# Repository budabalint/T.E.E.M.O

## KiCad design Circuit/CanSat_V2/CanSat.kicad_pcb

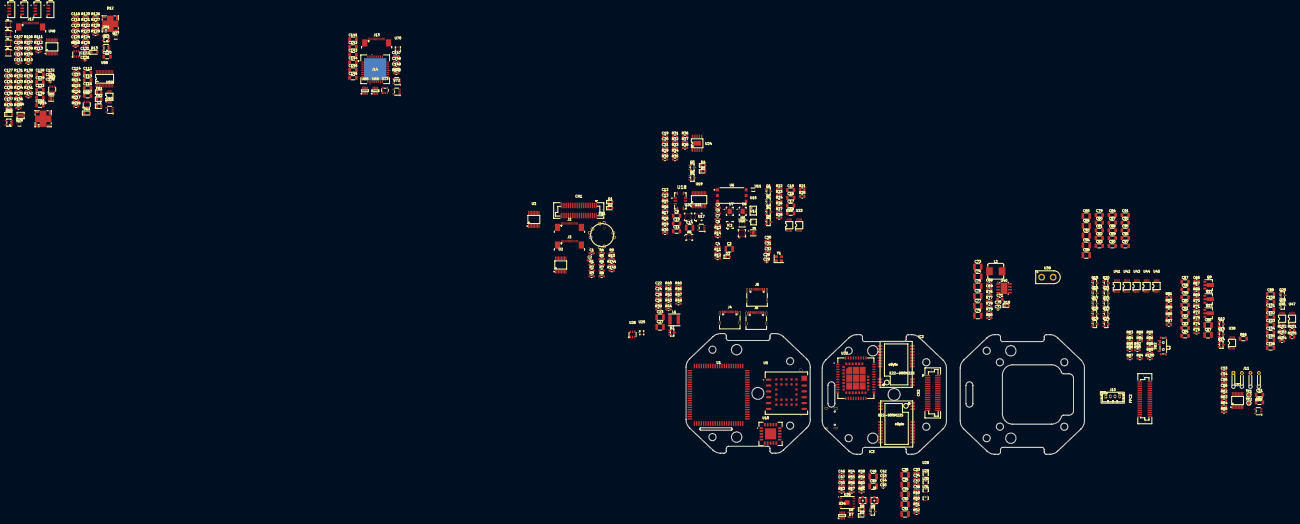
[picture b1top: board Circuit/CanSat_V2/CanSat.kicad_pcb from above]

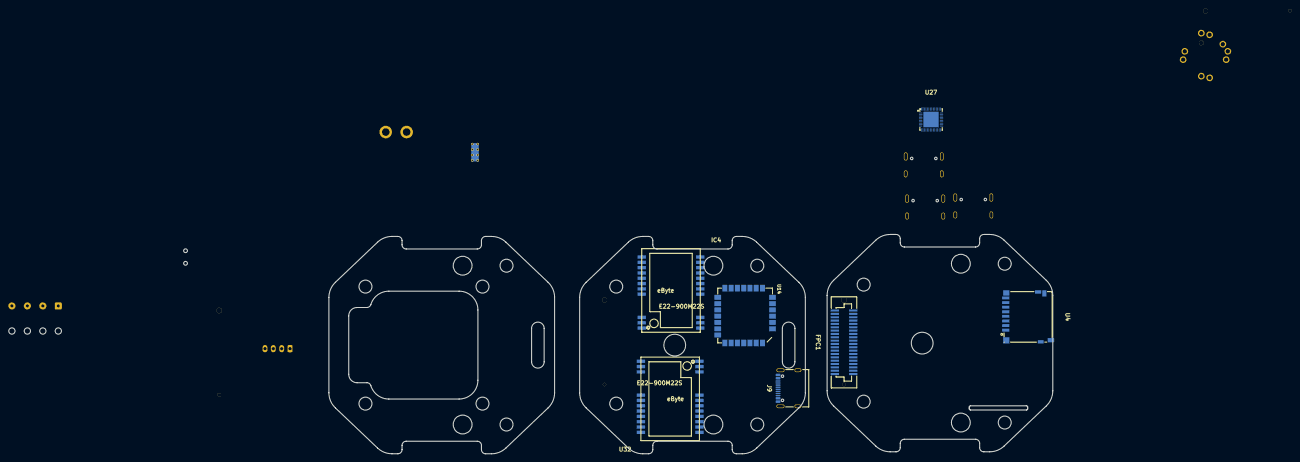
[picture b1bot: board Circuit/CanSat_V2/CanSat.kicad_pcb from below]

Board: 4 copper layers, 442 parts (7 on the bottom side), 345 nets, no tracks yet.

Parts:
C1, C2, C4, C5, C6, C7, C8, C12, C13, C19, C20, C21, C22, C24, C25, C26, C30, C31, C32, C33, C34, C37, C38, C46, C47, C50, C53, C54, C55, C56, C65, C68, C107, C108, C109, C110, C111, C114, C115, C118, C119, C123, C124, C125, C127, C130, C131, C135, C136, C137, C147, C148, C149: 100nF; C_0603_1608Metric_Pad1.08x0.95mm_HandSolder
C3, C14, C23, C27, C35, C36, C39, C40, C41, C48, C49, C66, C67, C73, C74, C75, C76, C77, C78, C85, C86, C93, C94, C98: 22uF; C_1210_3225Metric
C9, C10, C11, C15, C16, C17, C18, C51, C52, C57, C58, C59, C60, C61, C62, C63, C64, C79, C80, C81, C82, C83, C84, C87, C88, C89, C90, C91, C92, C95, C96, C97, C99, C100, C101, C102, C103, C104, C105, C106, C112, C113, C116, C117, C120, C128, C129, C133, C139, C140, C141, C142, C143, C144, C145, C146: 4.7uF; C_1206_3216Metric
C28, C29: 22pF; C_0402_1005Metric_Pad0.74x0.62mm_HandSolder
C42, C43, C44, C45: -; C_0402_1005Metric_Pad0.74x0.62mm_HandSolder
C69: 10nF; C_0603_1608Metric_Pad1.08x0.95mm_HandSolder
C70, C72: 68pF; C_0402_1005Metric_Pad0.74x0.62mm_HandSolder
C71: 1.2nF; C_0805_2012Metric_Pad1.18x1.45mm_HandSolder
C121: 10pF; C_0402_1005Metric_Pad0.74x0.62mm_HandSolder
C122: 47pF; C_0402_1005Metric_Pad0.74x0.62mm_HandSolder
C126, C138: 1nF; C_0402_1005Metric_Pad0.74x0.62mm_HandSolder
C132: 1pF; C_0402_1005Metric_Pad0.74x0.62mm_HandSolder
C134: 15pF; C_0402_1005Metric_Pad0.74x0.62mm_HandSolder
CN1, CN2: 61082-041402LF; CONN-SMD_61082-041402LF
D1, D2, D3, D4, D5, D8, D9, D10: LED; LED_0603_1608Metric_Pad1.05x0.95mm_HandSolder
D6, D7: ESD5311X-2/TR; D_0402_1005Metric_Pad0.77x0.64mm_HandSolder
D11: BAT54J; D_SOD-323_HandSoldering
D12, D14: SiPM; OPTO-SMD_4P-MICROFC-60035-SMT-TR
D13, D15: TECH PUBLIC BAS70WS; D_SOD-323_HandSoldering
FB1, FB2: FerriteBead_Small; D_0805_2012Metric
FPC1, FPC2: 61083-044402LF; FPC-SMD_40P-P0.80_61083-044402LF
IC1: ZMOD4510AI1V
IC2, IC3, IC4: E22-xxxM22S; E22-400M22S
J2, J3, J12, J13: Conn_01x15_Pin; TE_1-1734839-5_1x15-1MP_P0.5mm_Horizontal
J4, J5, J6, J9: USB_C; USB_C_Receptacle_Palconn_UTC16-G
J7, J8: U-Fl-IPEX; IPEX-SMD_4P-L2.6-W2.6-LS3.1
J10: VTX PWR; JST_PH_B4B-PH-K_1x04_P2.00mm_Vertical
J11: GLM-670; SolderWire-0.127sqmm_1x04_P3.7mm_D0.48mm_OD1mm_Relief
J14: FLIR_Lepton_Molex_1050281001; flir_CONN_1050282031_MOL
L1: SMNR4030-1R8MT; L_Taiyo-Yuden_NR-50xx
L2: FXL0630-3R3-M; L_Bourns_SRP7028A_7.3x6.6mm
L3: 47uh; D_0805_2012Metric
MT1: ICM-42670-P; XDCR_ICM-42670-P
Q1, Q3, Q15, Q16, Q19, Q20, Q23, Q25: AO3401A; SOT-23
Q2, Q4, Q5, Q6, Q7, Q8, Q10, Q17, Q18, Q21, Q22, Q24, Q26: BC817; SOT-23
Q9, Q11, Q12: WD070PG; SOT-89-3
Q13, Q14: AO3400A; SOT-23
Q27, Q28: XNRUSEMI XR2SK3019; SOT-523
R1, R121, R125, R129, R142: 33Ω; R_0603_1608Metric_Pad0.98x0.95mm_HandSolder
R2, R3, R4, R5: 2.2kΩ; R_0603_1608Metric_Pad0.98x0.95mm_HandSolder
R6, R10, R12: 220Ω; R_0603_1608Metric_Pad0.98x0.95mm_HandSolder
R7, R8, R9, R18, R19, R20, R22, R26, R29, R41, R55, R59, R67, R83, R84, R91, R92, R98, R102, R143, R144, R145: 47kΩ; R_0603_1608Metric_Pad0.98x0.95mm_HandSolder
R11, R24, R28, R34, R35, R36, R37, R46, R47, R48, R70, R71, R72, R87, R88, R95, R96, R100, R104, R122, R134: 10kΩ; R_0603_1608Metric_Pad0.98x0.95mm_HandSolder
R13: 18kΩ; R_0603_1608Metric_Pad0.98x0.95mm_HandSolder
R14, R38, R43, R128, R138, R139, R141: 100kΩ; R_0603_1608Metric_Pad0.98x0.95mm_HandSolder
R15: 20Ω; R_0603_1608Metric_Pad0.98x0.95mm_HandSolder
R16: 12.4Ω; R_0603_1608Metric_Pad0.98x0.95mm_HandSolder
R17: 42.2Ω; R_0603_1608Metric_Pad0.98x0.95mm_HandSolder
R21, R25, R81, R82, R89, R90, R97, R101, R105: shunt; R_0805_2012Metric
R23, R27, R58, R68, R69, R85, R86, R93, R94, R99, R103, R106, R107, R108, R109, R110, R111, R112, R113, R124: 4.7kΩ; R_0603_1608Metric_Pad0.98x0.95mm_HandSolder
R30, R31, R40, R42, R60, R61: 5.1kΩ; R_0603_1608Metric_Pad0.98x0.95mm_HandSolder
R32, R33, R56, R57, R62, R63, R64, R65, R73, R119, R123, R126, R127, R130, R136: 1kΩ; R_0603_1608Metric_Pad0.98x0.95mm_HandSolder
R39: 910kΩ; R_0603_1608Metric_Pad0.98x0.95mm_HandSolder
R44: 510kΩ; R_0603_1608Metric_Pad0.98x0.95mm_HandSolder
R45: 160kΩ; R_0603_1608Metric_Pad0.98x0.95mm_HandSolder
R49, R50, R51, R52, R80, R133: 100Ω; R_0603_1608Metric_Pad0.98x0.95mm_HandSolder
R53, R54: 0Ω; R_0603_1608Metric_Pad0.98x0.95mm_HandSolder
R66: shunt; R_1206_3216Metric
R74, R75: 200kΩ; R_0603_1608Metric_Pad0.98x0.95mm_HandSolder
R76: 10Ω; R_0603_1608Metric_Pad0.98x0.95mm_HandSolder
R77: 12kΩ; R_0603_1608Metric_Pad0.98x0.95mm_HandSolder
R78: 105kΩ; R_0603_1608Metric_Pad0.98x0.95mm_HandSolder
R79: 33kΩ; R_0603_1608Metric_Pad0.98x0.95mm_HandSolder
R114: 68kΩ; R_0603_1608Metric_Pad0.98x0.95mm_HandSolder
R115: 154kΩ; R_0603_1608Metric_Pad0.98x0.95mm_HandSolder
R116: 6,65kΩ; R_0603_1608Metric_Pad0.98x0.95mm_HandSolder
R117: 470kΩ; R_0603_1608Metric_Pad0.98x0.95mm_HandSolder
R118: 39kΩ; R_0603_1608Metric_Pad0.98x0.95mm_HandSolder
R120, R131: 470Ω; R_0603_1608Metric_Pad0.98x0.95mm_HandSolder
R132: 50Ω; R_0603_1608Metric_Pad0.98x0.95mm_HandSolder
R135: 680Ω; R_0603_1608Metric_Pad0.98x0.95mm_HandSolder
R137: 24kΩ; R_0603_1608Metric_Pad0.98x0.95mm_HandSolder
R140: 150kΩ; R_0603_1608Metric_Pad0.98x0.95mm_HandSolder
SW1: RKJXM1015001; SW-TH_RKJXM1015001
SW2: Power sw; SW_SPDT_PCM12
TP1: AIN1; TestPoint_Pad_D1.5mm
TP2: AIN2; TestPoint_Pad_D1.5mm
U1: ESP32-P4-Module; ESP32-P4
U2, U3: SN74LVC138ADGVR; TSSOP-16_L5.0-W4.4-P0.65-LS6.4-BL
U4: 114-00841-68; SIM-SMD_114-00841-68
U5: LC86G; XCVR_LC86G
U6: SFA 40; SFA40
U7: STC42A
U8: STC31-C-R3; STC42A
U9: SGP41-D-R4; XDCR_SGP41-D-R4
U10: SCD41-D-R2; XDCR_SCD41-D-R2
U11: SHT41-AD1B-R2; SHT4X
U12: BMP581; LGA-10_L2.0-W2.0-P0.50-TL_BMP581
U13: BME688; IC_BME688
U14: RadNano
U15: AS7331_M OLGA16 LF T&RDP; OLGA-16_L3.7-W2.6-P0.50-TL_AS7331-AQFM
U16: AS7343L-DLGM; LGA-16_L3.0-W3.0-P0.50-BL
U17, U36, U60, U71, U72: TPS7A2028DBV; SOT-23-5_L2.9-W1.6-P0.95-LS2.7-BR
U18: MICS-6814; SENSOR_MICS-6814
U19: AD7091R-4BRUZ; TSSOP-20_L6.5-W4.4-P0.65-LS6.4-BL
U20: H3LIS331DLTR; LGA-16_L3.0-W3.0-P0.50-BL_SQ
U21: MMC5983MA; LGA-16_L3.0-W3.0-P0.50-BL_SQ
U22, U23, U38, U41, U42, U43, U44, U45, U46, U47: INA226; VSSOP-10_L3.0-W3.0-P0.50-LS4.9-BL
U24: CH343K; ESSOP-10_L4.9-W3.9-P1.0-LS6.0-TL-EP
U25: TUSB321RWBR; X2QFN-12_L1.6-W1.6-P0.40-TL
U26: SY7072ABC; SOT-23-6_L2.9-W1.6-P0.95-LS2.8-BL
U27: CH9434A_C39831286; QFN-48_L5.0-W5.0-P0.35-TL-EP3.7-1
U28, U29, U30, U31: 74LVC1G04GV; SOT-353_L2.0-W1.2-P0.65-LS2.1-BL
U32: E28-2G4M27SX; E22-400M22S
U33: SIM7080G; XCVR_SIM7080G
U34, U68, U69: RS0102YH8; SOT-23-8_L3.0-W1.7-P0.65-LS2.8-BL
U35: MFF2-SIM; DFN-8-1EP_6x5mm_P1.27mm_EP2x2mm
U37: AD7799BRUZ-REEL; TSSOP-16_L5.0-W4.4-P0.65-LS6.4-BL
U39: XT30AW-M.G.Y; CONN-TH_XT30AW-M.G.Y
U40: AP64501SP-13; SOIC-8-1EP_3.9x4.9mm_P1.27mm_EP2.95x4.9mm_Mask2.71x3.4mm_Th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
U48: TCA9546APW; TSSOP-16_L5.0-W4.4-P0.65-LS6.4-BL
U49, U51, U53, U55: BME280; BME280_PSON65P250X250X100-8N
U50, U52, U54, U56: VEML7700-TT; XDCR_VEML7700-TT
U57: MAX5026EUT+T; SOT-23-6_L2.9-W1.6-P0.95-LS2.8-BL
U58: ADS8331IPWR; TSSOP-24_L7.8-W4.4-P0.65-LS6.4-BL
U59: DAC124S085CIMM/NOPB; VSSOP-10_L3.0-W3.0-P0.50-LS4.9-BL
U61, U62, U66: OPA365AIDBVR; SOT-23-5_L3.0-W1.7-P0.95-LS2.8-BR
U63, U67: TLV3501AIDBV; SOT-23-6_L2.9-W1.6-P0.95-LS2.9-BL
U64: LM27762DSSR; WSON-12_L3.0-W2.0-P0.50-BL-EP
U65: OPA858IDSGR; Texas_DSG0008A_WSON-8-1EP_2x2mm_P0.5mm_EP0.9x1.6mm
U70: TXB0104RUTR; UQFN-12_L2.0-W1.7-P0.40-BL
U73: TPS7A2012; SOT-23-5_L2.9-W1.6-P0.95-LS2.8-BL
Y1: 32Mhz; Crystal_SMD_3225-4Pin_3.2x2.5mm

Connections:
/Panel1_MCU/2G4MHZ_BUSY: CN1.32, U1.56 (GPIO29)
/Panel1_MCU/2G4MHZ_CS: CN1.18, U3.15 (Y0)
/Panel1_MCU/2G4MHZ_INT: CN1.31, U1.57 (GPIO30)
/Panel1_MCU/3.3V: CN1.1, R21.2, R25.2, U22.8 (Vbus), U22.10 (Vin+), U23.8 (Vbus), U23.10 (Vin+)
/Panel1_MCU/170MHZ_BUSY: CN1.26, U1.53 (GPIO26)
/Panel1_MCU/170MHZ_CS: CN1.24, U3.12 (Y3)
/Panel1_MCU/170MHZ_INT: CN1.25, U1.60 (GPIO33)
/Panel1_MCU/400MHZ_BUSY: CN1.28, U1.54 (GPIO27)
/Panel1_MCU/400MHZ_CS: CN1.22, U3.13 (Y2)
/Panel1_MCU/400MHZ_INT: CN1.27, U1.59 (GPIO32)
/Panel1_MCU/900MHZ_BUSY: CN1.30, U1.55 (GPIO28)
/Panel1_MCU/900MHZ_CS: CN1.20, U3.14 (Y1)
/Panel1_MCU/900MHZ_INT: CN1.29, U1.58 (GPIO31)
/Panel1_MCU/BARO_LP_CS: U2.11 (Y4), U21.4 (SPI_CS)
/Panel1_MCU/C6_BOOT: Q6.2 (E), R37.2, U1.9 (C6_IO9)
/Panel1_MCU/C6_Programmer/DTR: Q6.3 (C), R34.1, U24.6 (CTS/DTR)
/Panel1_MCU/C6_Programmer/RTS: Q5.2 (E), R35.1, U24.5 (RTS)
/Panel1_MCU/C6_Programmer/VBUS: C19.1, J4.A4 (VBUS), J4.A9 (VBUS), J4.B4 (VBUS), J4.B9 (VBUS), R29.2, U24.4 (VDD5)
/Panel1_MCU/C6_RX: D4.1 (K), U1.4 (C6_U0RXD), U24.9 (RXD)
/Panel1_MCU/C6_TX: D5.1 (K), U1.5 (C6_U0TXD), U24.8 (TXD)
/Panel1_MCU/ESP_RST: C21.1, R36.2, R38.1, U1.87 (ESP_EN)
/Panel1_MCU/G-FORCE_LP_CS: U2.12 (Y3), U20.8 (CS)
/Panel1_MCU/GLM_LP_CS: CN1.12, U2.15 (Y0)
/Panel1_MCU/GPS_RXD: U5.2 (TXD), U27.5 (RXD1)
/Panel1_MCU/GPS_TXD: U5.1 (RXD), U27.6 (TXD1)
/Panel1_MCU/High_Speed_USB_D+: J5.A6 (D+), J5.B6 (D+), U1.48 (USB_DM)
/Panel1_MCU/High_Speed_USB_D-: J5.A7 (D-), J5.B7 (D-), U1.49 (USB_DP)
/Panel1_MCU/I2C0_SCL: IC1.1 (SCL), J3.6, R2.1, U1.64 (GPIO37), U6.3 (SCL), U7.4 (SCL), U8.4 (SCL), U9.6 (SCL), U10.9 (SCL), U12.2 (SCK), U13.4 (SCK), U14.16, U15.13 (SCL), U16.2 (SCL)
/Panel1_MCU/I2C0_SDA: IC1.2 (SDA), J3.7, R3.1, U1.65 (GPIO38), U6.4 (SDA), U7.7 (SDA), U8.7 (SDA), U9.3 (SDA), U10.10 (SDA), U12.4 (SDI), U13.3 (SDI), U14.20, U15.12 (SDA), U16.8 (SDA)
/Panel1_MCU/I2C1_SCL: J2.3, R4.1, U1.67 (GPIO39)
/Panel1_MCU/I2C1_SDA: J2.4, R5.1, U1.68 (GPIO40)
/Panel1_MCU/I2C_Sensors/3.3V: C5.1, C6.1, C7.1, C8.1, IC1.5 (VDD), IC1.10 (VDDH), IC1.11 (RES_N), IC1.12 (VDDIO), R13.1, U6.1 (VDD), U6.2 (VSS), U7.6 (VDD), U8.3 (ADDR), U8.6 (VDD), U9.1 (VDD), U9.5 (VDDH), U10.7 (VDD), U10.19 (VDDH), U11.3 (VDD), U12.1 (VDDIO), U12.5 (SDO), U12.6 (CSB), U12.10 (VDD), U13.2 (CSB), U13.5 (SDO), U13.6 (VDDIO), U13.8 (VDD), U14.4 (ANSupply), U14.5 (Vdd), U14.6 (Vdd), U14.10 (Vdd), U14.17 (Vdd), U14.21 (Vdd), U15.3 (VDDA), U15.10 (VDDD), U16.1 (VDD)
/Panel1_MCU/ICM_LP_CS: MT1.12 (AP_CS), U2.13 (Y2)
/Panel1_MCU/LEPTON_MasterCLK: J3.14, U1.73 (GPIO45)
/Panel1_MCU/LEPTON_SPI3_CS: J3.10, U1.69 (GPIO41)
/Panel1_MCU/LEPTON_SPI3_MISO: J3.12, U1.71 (GPIO43)
/Panel1_MCU/LEPTON_SPI3_SCK: J3.11, U1.70 (GPIO42)
/Panel1_MCU/LEPTON_VSYNC: J3.9, MT1.7 (FSYNC), U1.72 (GPIO44)
/Panel1_MCU/LP_CS_DEMUX_A: U1.23 (GPIO8), U2.1 (A)
/Panel1_MCU/LP_CS_DEMUX_B: U1.24 (GPIO9), U2.2 (B)
/Panel1_MCU/LP_CS_DEMUX_C: U1.25 (GPIO10), U2.3 (C)
/Panel1_MCU/LP_I2C_SCL: CN1.8, U1.17 (GPIO2), U22.5 (SCL), U23.5 (SCL)
/Panel1_MCU/LP_I2C_SDA: CN1.10, U1.18 (GPIO3), U22.4 (SDA), U23.4 (SDA)
/Panel1_MCU/LP_MISO: CN1.11, MT1.1 (AP_SDO/AP_AD0), U1.19 (GPIO4), U19.17 (SDO), U20.7 (SDO/SA0), U21.5 (SPI_SDO)
/Panel1_MCU/LP_MOSI: CN1.9, MT1.14 (AP_SDA/AP_SDIO/AP_SDI), U1.20 (GPIO5), U19.16 (SDI), U20.6 (SDA/SDI/SDO), U21.16 (SDA/SPI_SDI)
/Panel1_MCU/LP_SCK: CN1.7, MT1.13 (AP_SCL/AP_SCLK), U1.22 (GPIO7), U19.18 (SCLK), U20.4 (SCL/SPS), U21.1 (SCL/SPI_SCK)
/Panel1_MCU/Lepton_PWR: C15.1, C16.1, J3.1, J3.2, Q1.3 (D)
/Panel1_MCU/MICS_CONVST: U1.26 (GPIO11), U19.19 (~CONVST)
/Panel1_MCU/MICS_LP_CS: U2.14 (Y1), U19.1 (~CS)
/Panel1_MCU/P4_Dual_USB/Standby_3.3V: C24.2, C26.1, C27.1, L1.2, R47.1, R48.2, U25.12 (VDD), U26.6 (IN)
/Panel1_MCU/P4_Dual_USB/USB_ID: R46.1, R47.2, U25.9 (ID)
/Panel1_MCU/P4_Dual_USB/VBUS: C22.1, C23.1, C25.1, J5.A4 (VBUS), J5.A9 (VBUS), J5.B4 (VBUS), J5.B9 (VBUS), J6.A4 (VBUS), J6.A9 (VBUS), J6.B4 (VBUS), J6.B9 (VBUS), R39.1, R41.2, R44.1, U26.5 (OUT)
/Panel1_MCU/P4_Dual_USB/VBUS_DET: R39.2, R43.1, U25.5 (VBUS_DET)
/Panel1_MCU/PROG_USB_D+: J6.A6 (D+), J6.B6 (D+), U1.51 (GPIO25)
/Panel1_MCU/PROG_USB_D-: J6.A7 (D-), J6.B7 (D-), U1.50 (GPIO24)
/Panel1_MCU/RADIO_CS_DEMUX_A: U1.77 (GPIO49), U3.1 (A)
/Panel1_MCU/RADIO_CS_DEMUX_B: U1.78 (GPIO50), U3.2 (B)
/Panel1_MCU/RADIO_CS_DEMUX_C: U1.79 (GPIO51), U3.3 (C)
/Panel1_MCU/RANGE _RXD: CN1.38, U27.38 (RXD2)
/Panel1_MCU/RANGE_TXD: CN1.37, U27.4 (TXD2)
/Panel1_MCU/Radio_MISO: CN1.19, U1.61 (GPIO34), U27.43 (SDO)
/Panel1_MCU/Radio_MOSI: CN1.17, U1.62 (GPIO35), U27.44 (SDI)
/Panel1_MCU/Radio_SCK: CN1.15, U1.63 (GPIO36), U27.45 (SCK)
/Panel1_MCU/SD_CLK: R145.1, U1.75 (GPIO47), U4.5 (CLK)
/Panel1_MCU/SD_CMD: R144.1, U1.74 (GPIO46), U4.3 (CMD)
/Panel1_MCU/SD_DATA0: U1.76 (GPIO48), U4.7 (DAT0)
/Panel1_MCU/SIM7080_RXD: CN1.36, U27.20 (RXD0)
/Panel1_MCU/SIM7080_TXD: CN1.35, U27.17 (TXD0)
/Panel1_MCU/SPI_Sensors/ADC_IN: U19.7 (MUXOUT), U19.14 (ADCIN)
/Panel1_MCU/SPI_Sensors/CH_out: R19.2, U18.B, U19.9 (VIN2)
/Panel1_MCU/SPI_Sensors/NH3_out: R18.2, U18.C, U19.8 (VIN0)
/Panel1_MCU/SPI_Sensors/NO2_out: R20.2, U18.K, U19.13 (VIN1)
/Panel1_MCU/SPI_Sensors/heater_voltage: C11.2, C12.2, R15.1, R16.1, R17.1, U17.5 (OUT), U18.A, U18.F, U18.H, U19.5 (REFIN/REFOUT)
/Panel1_MCU/SPI_UART_CS: U3.11 (Y4), U27.46 (~SCS)
/Panel1_MCU/Sensors_3.3V: C1.2, C2.2, C3.1, C4.1, C9.2, C13.1, C30.2, CN1.2, MT1.5 (VDDIO), MT1.8 (VDD), R1.2, R6.2, R7.1, R8.2, R9.1, R10.2, R11.1, R144.2, R145.2, U2.6 (G1), U2.16 (VCC), U3.6 (G1), U3.16 (VCC), U4.4 (VDD), U5.4 (VCC), U5.5 (V_BCKP), U17.1 (IN), U17.3 (EN), U19.2 (~RESET), U19.3 (VDD), U19.20 (VDRIVE), U20.1 (Vdd_IO), U20.14 (Vdd), U21.2 (VDD), U21.13 (VDDIO), U27.3 (VCC)
/Panel1_MCU/SiPM_3.3V: C17.1, C18.1, J2.1, Q3.3 (D)
/Panel1_MCU/Standby_3.3V: C20.1, CN1.3, CN1.4, R2.2, R3.2, R4.2, R5.2, R24.1, R28.1, R32.1, R33.1, R37.1, R38.2, U1.66 (ESP_LDO_VO4), U1.84 (VBAT), U1.85 (ESP_3V3), U1.86 (ESP_3V3), U22.2 (A0), U22.6 (VS), U23.2 (A0), U23.6 (VS), U24.7 (VIO), U24.10 (V3)
/Panel1_MCU/VTX_RXD: CN1.40, U27.36 (RXD3)
/Panel1_MCU/VTX_TXD: CN1.39, U27.37 (TXD3)
/Panel2_COM/2G4MHZ_BUSY: CN2.32, U32.14 (BUSY)
/Panel2_COM/2G4MHZ_CS: CN2.18, U32.19 (NSS)
/Panel2_COM/2G4MHZ_DIO2: R51.2, U30.2 (A), U32.8 (DIO2)
/Panel2_COM/2G4MHZ_INT: CN2.31, U32.13 (DIO1)
/Panel2_COM/2G4MHZ_RXEN: U30.4 (Y), U32.6 (RXEN)
/Panel2_COM/2G4MHZ_TXEN: R51.1, U32.7 (TXEN)
/Panel2_COM/3.3V: CN2.1, FPC1.1
/Panel2_COM/170MHZ_BUSY: CN2.26, IC3.14 (BUSY)
/Panel2_COM/170MHZ_CS: CN2.24, IC3.19 (NSS)
/Panel2_COM/170MHZ_DIO2: IC3.8 (DIO2), R50.2, U29.2 (A)
/Panel2_COM/170MHZ_INT: CN2.25, IC3.13 (DIO1)
/Panel2_COM/170MHZ_RXEN: IC3.6 (RXEN), U29.4 (Y)
/Panel2_COM/170MHZ_TXEN: IC3.7 (TXEN), R50.1
/Panel2_COM/400MHZ_BUSY: CN2.28, IC4.14 (BUSY)
/Panel2_COM/400MHZ_CS: CN2.22, IC4.19 (NSS)
/Panel2_COM/400MHZ_DIO2: IC4.8 (DIO2), R52.2, U31.2 (A)
/Panel2_COM/400MHZ_INT: CN2.27, IC4.13 (DIO1)
/Panel2_COM/400MHZ_RXEN: IC4.6 (RXEN), U31.4 (Y)
/Panel2_COM/400MHZ_TXEN: IC4.7 (TXEN), R52.1
/Panel2_COM/900MHZ_BUSY: CN2.30, IC2.14 (BUSY)
/Panel2_COM/900MHZ_CS: CN2.20, IC2.19 (NSS)
/Panel2_COM/900MHZ_DIO2: IC2.8 (DIO2), R49.2, U28.2 (A)
/Panel2_COM/900MHZ_INT: CN2.29, IC2.13 (DIO1)
/Panel2_COM/900MHZ_RXEN: IC2.6 (RXEN), U28.4 (Y)
/Panel2_COM/900MHZ_TXEN: IC2.7 (TXEN), R49.1
/Panel2_COM/GLM_LP_CS: CN2.12, FPC1.12
/Panel2_COM/HARD_RESET: CN2.14, FPC1.14
/Panel2_COM/LP_I2C_SCL: CN2.8, FPC1.8
/Panel2_COM/LP_I2C_SDA: CN2.10, FPC1.10
/Panel2_COM/LP_MISO: CN2.11, FPC1.11
/Panel2_COM/LP_MOSI: CN2.9, FPC1.9
/Panel2_COM/LP_SCK: CN2.7, FPC1.7
/Panel2_COM/LTE_modem/1.8V: R55.1, U33.40 (VDD_EXT), U34.4 (OE), U34.8 (VCCA)
/Panel2_COM/LTE_modem/NETLIGHT: R56.1, U33.41 (NETLIGHT)
/Panel2_COM/LTE_modem/RF_GNSS: C43.2, R54.1, U33.68 (GNSS_ANT)
/Panel2_COM/LTE_modem/RF_LTE: C42.1, R53.1, U33.32 (RF_ANT)
/Panel2_COM/LTE_modem/SIM_CLK: U33.16 (SIM_CLK), U35.3 (CLK)
/Panel2_COM/LTE_modem/SIM_DATA: U33.15 (SIM_DATA), U35.7 (I/O)
/Panel2_COM/LTE_modem/SIM_RST: U33.17 (SIM_RST), U35.2 (RST)
/Panel2_COM/LTE_modem/SIM_VDD: C50.1, U33.18 (SIM_VDD), U35.1 (VCC)
/Panel2_COM/LTE_modem/STATUS: R57.1, U33.42 (STATUS)
/Panel2_COM/LTE_modem/USB_D+: J9.A6 (D+), J9.B6 (D+), U33.25 (USB_DP)
/Panel2_COM/LTE_modem/USB_D-: J9.A7 (D-), J9.B7 (D-), U33.26 (USB_DM)
/Panel2_COM/LTE_modem/VBUS: C46.1, J9.A4 (VBUS), J9.A9 (VBUS), J9.B4 (VBUS), J9.B9 (VBUS), R59.2, U33.24 (USB_VBUS)
/Panel2_COM/LTE_modem_PWR: FPC1.15, FPC1.17, R58.2
/Panel2_COM/RADIO_RST: CN2.21, IC2.15 (NRST), IC3.15 (NRST), IC4.15 (NRST), U32.15 (NRST)
/Panel2_COM/Radio_2.4Ghz_PWR: C37.2, C39.1, C41.1, FPC1.31, FPC1.33, U32.9 (VCC)
/Panel2_COM/Radio_170Mhz_PWR: C34.2, C36.1, FPC1.24, FPC1.26, IC3.9 (VCC)
/Panel2_COM/Radio_400Mhz_PWR: C38.2, C40.1, FPC1.23, FPC1.25, IC4.9 (VCC)
/Panel2_COM/Radio_900Mhz_PWR: C33.2, C35.1, FPC1.32, FPC1.34, IC2.9 (VCC)
/Panel2_COM/Radio_MISO: CN2.19, IC2.16 (MISO), IC3.16 (MISO), IC4.16 (MISO), U32.16 (MISO)
/Panel2_COM/Radio_MOSI: CN2.17, IC2.17 (MOSI), IC3.17 (MOSI), IC4.17 (MOSI), U32.17 (MOSI)
/Panel2_COM/Radio_SCK: CN2.15, IC2.18 (SCK), IC3.18 (SCK), IC4.18 (SCK), U32.18 (SCK)
/Panel2_COM/SIM7080_PWRKEY: CN2.23, U34.2 (B1)
/Panel2_COM/Sensors_3.3V: CN2.2, FPC1.2, U28.5 (VCC), U29.5 (VCC), U30.5 (VCC), U31.5 (VCC)
/Panel2_COM/Standby_3.3V: CN2.3, CN2.4, FPC1.3, FPC1.4
/Panel2_COM/VTX_UART3_RXD: CN2.40, FPC1.40, U34.3 (B2)
/Panel3_GLM-PSU/3.3V_PSU/3.3V: C72.1, C73.2, C74.2, C75.2, C76.2, C77.1, C78.1, L2.2, R78.1, R80.1, R81.2, R82.2, R89.2, R90.2, R97.2, R101.2, R105.2, U41.8 (Vbus), U41.10 (Vin+), U42.8 (Vbus), U42.10 (Vin+), U43.8 (Vbus), U43.10 (Vin+), U44.8 (Vbus), U44.10 (Vin+), U45.8 (Vbus), U45.10 (Vin+), U46.8 (Vbus), U46.10 (Vin+), U47.8 (Vbus), U47.10 (Vin+)
/Panel3_GLM-PSU/3.3V_PSU/Input-Voltage: C57.1, C59.1, C61.1, C63.1, Q11.2 (D), Q12.2 (D), R66.2, U38.8 (Vbus), U38.10 (Vin+), U40.2 (VIN), U40.3 (EN)
/Panel3_GLM-PSU/GLM_670/2.8V: C52.1, C53.1, C54.1, J11.2, U36.5 (OUT), U37.9 (REFIN(+)), U37.13 (AVDD)
/Panel3_GLM-PSU/GLM_670/AIN1: R62.1, TP1.1 (1_1), U37.7 (AIN2(+))
/Panel3_GLM-PSU/GLM_670/AIN2: R63.1, TP2.1 (1_1), U37.3 (AIN3(+)P1)
/Panel3_GLM-PSU/GLM_670/GLM_GND: J11.1, U37.10 (REFIN(-)), U37.11 (PSW)
/Panel3_GLM-PSU/GLM_LP_CS: FPC2.12, U37.2 (CS)
/Panel3_GLM-PSU/HARD_RESET: FPC2.14, R72.1, R73.1
/Panel3_GLM-PSU/LP_I2C_SCL: FPC2.8, U38.5 (SCL), U41.5 (SCL), U42.2 (A0), U42.5 (SCL), U43.5 (SCL), U44.5 (SCL), U45.5 (SCL), U46.5 (SCL), U47.5 (SCL)
/Panel3_GLM-PSU/LP_I2C_SDA: FPC2.10, U38.2 (A0), U38.4 (SDA), U41.4 (SDA), U42.4 (SDA), U43.1 (A1), U43.4 (SDA), U44.4 (SDA), U45.2 (A0), U45.4 (SDA), U46.4 (SDA), U47.4 (SDA)
/Panel3_GLM-PSU/LP_MISO: FPC2.11, U37.15 (DOUTRDY)
/Panel3_GLM-PSU/LP_MOSI: FPC2.9, U37.16 (DIN)
/Panel3_GLM-PSU/LP_SCK: FPC2.7, U37.1 (SCLK)
/Panel3_GLM-PSU/LTE_modem_PWR: C79.1, C81.1, C83.1, C85.1, FPC2.15, FPC2.17, Q15.3 (D)
/Panel3_GLM-PSU/Power_Connector/GATE: Q11.1 (G), Q12.1 (G), R71.2, SW2.1
/Panel3_GLM-PSU/Radio_2.4Ghz_PWR: C87.1, C89.1, C91.1, C93.1, FPC2.31, FPC2.33, Q19.3 (D)
/Panel3_GLM-PSU/Radio_170Mhz_PWR: C88.1, C90.1, C92.1, C94.1, FPC2.24, FPC2.26, Q20.3 (D)
/Panel3_GLM-PSU/Radio_400Mhz_PWR: C95.1, C96.1, C97.1, C98.1, FPC2.23, FPC2.25, Q23.3 (D)
/Panel3_GLM-PSU/Radio_900Mhz_PWR: C80.1, C82.1, C84.1, C86.1, FPC2.32, FPC2.34, Q16.3 (D)
/Panel3_GLM-PSU/Sensors_3.3V: C99.1, C100.1, C101.1, C102.1, FPC2.2, Q25.3 (D)
/Panel3_GLM-PSU/Standby_3.3V: C51.1, C55.1, C103.1, C104.1, C105.1, C106.1, FPC2.3, FPC2.4, R70.1, R87.1, R88.1, R95.1, R96.1, R100.1, R104.1, R105.1, U36.1 (IN), U36.3 (EN), U37.14 (DVDD), U38.6 (VS), U41.1 (A1), U41.6 (VS), U42.1 (A1), U42.6 (VS), U43.6 (VS), U44.1 (A1), U44.2 (A0), U44.6 (VS), U45.1 (A1), U45.6 (VS), U46.2 (A0), U46.6 (VS), U47.6 (VS), U47.9 (Vin-)
/Panel3_GLM-PSU/VTX_PWR: C58.1, C60.1, C62.1, C64.1, J10.1, Q9.2 (D)
/Panel3_GLM-PSU/VTX_UART3_RXD: FPC2.40, J10.4
/Panel3_GLM-PSU/VTX_UART3_TXD: FPC2.39, J10.3
/Panel4_BAT_Plate/GAMMA_INT: J12.13, R128.2, U63.5 (out)
/Panel4_BAT_Plate/I2C1_SCL: J12.3, U48.14 (SCL)
/Panel4_BAT_Plate/I2C1_SDA: J12.4, U48.15 (SDA)
/Panel4_BAT_Plate/MUON_INT: J12.14, R139.2, U67.5 (out)
/Panel4_BAT_Plate/SCL_0: R107.1, U48.5 (SC0), U49.4 (SCK), U50.1 (SCL)
/Panel4_BAT_Plate/SCL_1: R109.1, U48.7 (SC1), U53.4 (SCK), U54.1 (SCL)
/Panel4_BAT_Plate/SCL_2: R111.1, U48.10 (SC2), U51.4 (SCK), U52.1 (SCL)
/Panel4_BAT_Plate/SCL_3: R113.1, U48.12 (SC3), U55.4 (SCK), U56.1 (SCL)
/Panel4_BAT_Plate/SDA_0: R106.1, U48.4 (SD0), U49.2 (CSB), U50.4 (SDA)
/Panel4_BAT_Plate/SDA_1: R108.1, U48.6 (SD1), U53.3 (SDI), U54.4 (SDA)
/Panel4_BAT_Plate/SDA_2: R110.1, U48.9 (SD2), U51.3 (SDI), U52.4 (SDA)
/Panel4_BAT_Plate/SDA_3: R112.1, U48.11 (SD3), U55.3 (SDI), U56.4 (SDA)
/Panel4_BAT_Plate/SPI_CS_1: J12.7, U59.9 (~SYNC)
/Panel4_BAT_Plate/SPI_CS_2: J12.8, U58.11 (FS/~CS)
/Panel4_BAT_Plate/SPI_MISO: J12.11, U58.13 (SDO)
/Panel4_BAT_Plate/SPI_MOSI: J12.10, U58.12 (SDI), U59.8 (DIN)
/Panel4_BAT_Plate/SPI_SCK: J12.9, U58.10 (SCLK), U59.10 (SCLK)
/Panel4_BAT_Plate/SiPM_detectors/2.8V: C117.1, U58.18 (REF+), U59.7 (VREFIN), U60.5 (OUT)
/Panel4_BAT_Plate/SiPM_detectors/COMP: R114.1, U59.2 (VOUTA)
/Panel4_BAT_Plate/SiPM_detectors/Gamma Ch/+3.3V: C119.2, C120.2, C124.2, C125.2, FB1.1, U61.5 (V+), U62.5 (V+), U63.4 (V+), U63.6 (SHDN)
/Panel4_BAT_Plate/SiPM_detectors/Gamma Ch/+30V: C113.1, C114.1, D11.1 (K), R115.1, R117.1, R119.1, R130.1
/Panel4_BAT_Plate/SiPM_detectors/Gamma Ch/OPA365-out: R129.1, U62.1, U62.4 (-)
/Panel4_BAT_Plate/SiPM_detectors/Gamma Ch/opa365_in-: C121.2, R123.2, R124.2, U61.4 (-)
/Panel4_BAT_Plate/SiPM_detectors/Gamma_Thres: R127.1, U59.4 (VOUTC)
/Panel4_BAT_Plate/SiPM_detectors/MAX_COMP: C115.1, R117.2, R118.1, U58.3 (IN3)
/Panel4_BAT_Plate/SiPM_detectors/Muon_Thres: C135.1, U59.3 (VOUTB), U67.1 (-)
/Panel4_BAT_Plate/SiPM_detectors/Müon Ch/+3.3V: C128.1, C136.2, C137.2, FB2.1, U64.3 (VIN), U64.8 (EN–), U64.12 (EN+), U66.5 (V+), U67.4 (V+), U67.6 (SHDN)
/Panel4_BAT_Plate/SiPM_detectors/Müon Ch/FB+: R140.1, R141.2, U64.2 (FB+)
/Panel4_BAT_Plate/SiPM_detectors/Müon Ch/FB–: R137.1, R138.2, U64.7 (FB–)
/Panel4_BAT_Plate/SiPM_detectors/Müon Ch/OPA365-out: R142.1, U66.1, U66.4 (-)
/Panel4_BAT_Plate/SiPM_detectors/Müon Ch/opa858_V+: C130.2, C139.1, R140.2, U64.11 (OUT+), U65.7 (V+), U65.8 (~PD)
/Panel4_BAT_Plate/SiPM_detectors/Müon Ch/opa858_V-: C131.2, C140.1, R137.2, U64.6 (OUT–), U65.5 (V-), U65.9 (V-)
/Panel4_BAT_Plate/SiPM_detectors/Müon Ch/opa858_in-: C132.2, R133.2, R135.2, U65.3 (-)
/Panel4_BAT_Plate/SiPM_detectors/Müon_ADC: C138.1, R142.2, U58.1 (IN1)
/Panel4_BAT_Plate/SiPM_detectors/RESET: R120.1, R131.1
/Panel4_BAT_Plate/TCA_RST: J12.6, U48.3 (~RESET)
/Panel5_FLIR/1.2V: C146.2, C149.2, J14.7 (VDDC_1.2V), U73.5 (OUT)
/Panel5_FLIR/2.8V_1: C144.2, C147.2, J14.16 (VDDIO), J14.23 (PWR_DWN_L), U68.4 (OE), U68.8 (VCCA), U69.4 (OE), U69.8 (VCCA), U70.1 (VCCA), U70.12 (OE), U71.5 (OUT)
/Panel5_FLIR/2.8V_2: C145.2, C148.2, J14.19 (VDD_2.8V), U72.5 (OUT)
/Panel5_FLIR/GPIO3_VSYNC: J14.2 (GPIO3_VSYNC), U70.3 (A2)
/Panel5_FLIR/I2C0_SCL: J13.6, U68.2 (B1)
/Panel5_FLIR/I2C0_SDA: J13.7, U68.3 (B2)
/Panel5_FLIR/LEPTON_MasterCLK: J13.14, U70.7 (B4)
/Panel5_FLIR/LEPTON_PWR_EN: J13.4, R143.1, U71.3 (EN), U72.3 (EN), U73.3 (EN)
/Panel5_FLIR/LEPTON_RST: J13.5, U69.2 (B1)
/Panel5_FLIR/LEPTON_SPI3_CS: J13.10, U69.3 (B2)
/Panel5_FLIR/LEPTON_SPI3_MISO: J13.12, U70.8 (B3)
/Panel5_FLIR/LEPTON_SPI3_SCK: J13.11, U70.10 (B1)
/Panel5_FLIR/LEPTON_VSYNC: J13.9, U70.9 (B2)
/Panel5_FLIR/Lepton_PWR: C141.2, C142.2, C143.2, J13.1, J13.2, U70.11 (VCCB), U71.1 (IN), U72.1 (IN), U73.1 (IN)
/Panel5_FLIR/MASTER_CLK: J14.26 (MASTER_CLK), U70.2 (A1)
/Panel5_FLIR/RESET_L: J14.24 (RESET_L), U69.7 (A1)
/Panel5_FLIR/SCL: J14.21 (SCL), U68.7 (A1)
/Panel5_FLIR/SDA: J14.22 (SDA), U68.6 (A2)
/Panel5_FLIR/SPI_CLK: J14.13 (SPI_CLK), U70.5 (A4)
/Panel5_FLIR/SPI_CS_L: J14.14 (SPI_CS_L), U69.6 (A2)
/Panel5_FLIR/SPI_MISO: J14.12 (SPI_MISO), U70.4 (A3)
GND: C1.1, C2.1, C3.2, C4.2, C5.2, C6.2, C7.2, C8.2, C9.1, C10.2, C11.1, C12.1, C13.2, C14.1, C15.2, C16.2, C17.2, C18.2, C19.2, C20.2, C21.2, C22.2, C23.2, C24.1, C25.2, C26.2, C27.2, C28.1, C29.1, C30.1, C31.1, C32.2, C33.1, C34.1, C35.2, C36.2, C37.1, C38.1, C39.2, C40.2, C41.2, C42.2, C43.1, C44.2, C45.1, C46.2, C47.2, C48.2, C49.2, C50.2, C51.2, C52.2, C53.2, C54.2, C55.2, C57.2, C58.2, C59.2, C60.2, C61.2, C62.2, C63.2, C64.2, C65.2, C66.2, C67.2, C69.2, C70.2, C71.2, C73.1, C74.1, C75.1, C76.1, C77.2, C78.2, C79.2, C80.2, C81.2, C82.2, C83.2, C84.2, C85.2, C86.2, C87.2, C88.2, C89.2, C90.2, C91.2, C92.2, C93.2, C94.2, C95.2, C96.2, C97.2, C98.2, C99.2, C100.2, C101.2, C102.2, C103.2, C104.2, C105.2, C106.2, C107.1, C107.2, C108.1, C108.2, C109.1, C109.2, C110.1, C110.2, C111.1, C111.2, C112.1, C112.2, C113.2, C114.2, C115.2, C116.1, C116.2, C117.2, C118.2, C119.1, C120.1, C122.2, C123.2, C124.1, C125.1, C126.2, C127.2, C128.2, C129.2, C130.1, C131.1, C134.2, C135.2, C136.1, C137.1, C138.2, C139.2, C140.2, C141.1, C142.1, C143.1, C144.1, C145.1, C146.1, C147.1, C148.1, C149.1, CN1.5, CN1.6, CN1.13, CN1.16, CN1.33, CN1.34, CN2.5, CN2.6, CN2.13, CN2.16, CN2.33, CN2.34, D3.1 (K), D6.2, D7.2, D8.1 (K), D9.1 (K), D10.1 (K), FB1.2, FB2.2, FPC1.5, FPC1.6, FPC1.13, FPC1.16, FPC1.18, FPC1.19, FPC1.20, FPC1.21, FPC1.22, FPC1.27, FPC1.28, FPC1.29, FPC1.30, FPC1.35, FPC1.36, FPC1.37, FPC1.38, FPC2.5, FPC2.6, FPC2.13, FPC2.16, FPC2.18, FPC2.19, FPC2.20, FPC2.21, FPC2.22, FPC2.27, FPC2.28, FPC2.29, FPC2.30, FPC2.35, FPC2.36, FPC2.37, FPC2.38, IC1.6 (VSS_1), IC1.7 (VSS_2), IC1.9 (VSS_3), IC2.1 (GND), IC2.2 (GND), IC2.3 (GND), IC2.4 (GND), IC2.5 (GND), IC2.10 (GND), IC2.11 (GND), IC2.12 (GND), IC2.20 (GND), IC2.22 (GND), IC3.1 (GND), IC3.2 (GND), IC3.3 (GND), IC3.4 (GND), IC3.5 (GND), IC3.10 (GND), IC3.11 (GND), IC3.12 (GND), IC3.20 (GND), IC3.22 (GND), IC4.1 (GND), IC4.2 (GND), IC4.3 (GND), IC4.4 (GND), IC4.5 (GND), IC4.10 (GND), IC4.11 (GND), IC4.12 (GND), IC4.20 (GND), IC4.22 (GND), J2.2, J2.12, J2.15, J3.3, J3.8, J3.13, J3.15, J4.A1 (GND), J4.A12 (GND), J4.B1 (GND), J4.B12 (GND), J5.A1 (GND), J5.A12 (GND), J5.B1 (GND), J5.B12 (GND), J6.A1 (GND), J6.A12 (GND), J6.B1 (GND), J6.B12 (GND), J7.2 (Ext), J8.2 (Ext), J9.A1 (GND), J9.A12 (GND), J9.B1 (GND), J9.B12 (GND), J10.2, J12.1, J12.2, J12.12, J12.15, J13.3, J13.8, J13.13, J13.15, J14.1 (GND), J14.6 (GND), J14.8 (GND), J14.9 (GND), J14.10 (GND), J14.11 (SPI_MOSI), J14.15 (GND), J14.18 (GND), J14.20 (GND), J14.25 (GND), J14.27 (GND), J14.30 (GND), L3.2, MT1.6 (GND), Q2.2 (E), Q4.2 (E), Q7.2 (E), Q8.2 (E), Q10.3 (E), Q13.2 (S), Q14.2 (S), Q17.2 (E), Q18.2 (E), Q21.2 (E), Q22.2 (E), Q24.2 (E), Q26.3 (E), Q27.2 (S), Q28.2 (S), R14.1, R18.1, R19.1, R20.1, R29.1, R30.1, R31.1, R40.1, R41.1, R42.1, R43.2, R45.2, R59.1, R60.1, R61.1, R62.2, R63.2, R72.2, R75.2, R79.2, R116.2, R118.2, R121.2, R122.1, R123.1, R132.2, R133.1, R134.1, R138.1, R141.1, R143.2, SW1.COM, SW1.GND, U1.1 (GND), U1.3 (GND), U1.15 (GND), U1.33 (GND), U1.40 (GND), U1.47 (GND), U1.52 (GND), U1.83 (GND), U2.4 (~G2A), U2.5 (~G2B), U2.8 (GND), U3.4 (~G2A), U3.5 (~G2B), U3.8 (GND), U4.6 (VSS), U4.9 (CD1), U4.10 (CD2), U4.11 (EH), U4.12 (EH), U4.13 (EH), U4.14 (EH), U5.3 (GND), U5.12 (GND), U5.13 (GND), U5.14 (GND), U5.15 (GND), U5.16 (GND), U5.17 (GND), U5.18 (GND), U5.19 (GND), U5.20 (GND), U5.21 (GND), U5.22 (GND), U5.23 (GND), U5.24 (GND), U5.25 (GND), U5.26 (GND), U5.27 (GND), U5.28 (GND), U5.29 (GND), U5.30 (GND), U5.31 (GND), U5.32 (GND), U5.33 (GND), U5.34 (GND), U5.35 (GND), U5.36 (GND), U6.6 (VSS), U7.5 (VSS), U7.13 (EXP), U8.1 (VSS), U8.5 (VSS), U8.9 (VSS), U8.11 (VSS), U8.13 (EXP), U9.2 (VSS), U9.7 (EXP), U10.6 (GND), U10.20 (GND), U10.21 (GND), U11.4 (VSS), U12.3 (VSS), U12.8 (VSS), U13.1 (GND), U13.7 (GND), U14.1 (GND), U14.2 (GND), U14.3 (GND), U14.8 (GND), U14.9 (GND), U14.11 (GND), U14.15, U14.18, U14.24 (GND), U14.25 (GND), U14.26 (GND), U14.27 (GND), U15.1 (VSSA), U15.2 (VSSA), U15.5 (VSSA), U15.6 (VSSA), U15.7 (A1), U15.8 (SYN), U15.11 (VSSD), U15.14 (A0), U15.15 (VSSA), U15.16 (VSSA), U16.3 (GND), U16.5 (PGND), U17.2 (GND), U18.D, U19.6 (GND), U19.15 (GND), U20.5 (GND), U20.10 (Reserved), U20.12 (GND), U20.13 (GND), U20.15 (Reserved), U20.16 (GND), U21.9 (GND), U21.11 (GND), U22.1 (A1), U22.7 (GND)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
unnamed: C31.2, U27.1 (VDD), U27.2 (VDD), U27.35 (VDD)
unnamed: C68.2, R76.2
unnamed: C71.1, R77.2
unnamed: C118.1, R119.2
unnamed: C121.1, R124.1, R125.2, R126.1, U61.1
unnamed: C126.1, R129.2
unnamed: C127.1, R130.2
unnamed: D1.2 (A), R6.1
unnamed: D1.1 (K), U2.7 (Y7)
unnamed: D2.2 (A), R10.1
unnamed: D2.1 (K), U3.7 (Y7)
unnamed: D3.2 (A), R12.1
unnamed: D4.2 (A), R32.2
unnamed: D5.2 (A), R33.2
unnamed: D8.2 (A), R56.2
unnamed: D9.2 (A), R57.2
unnamed: D10.2 (A), R80.2
unnamed: D11.2 (A), L3.1, U57.6 (LX)
unnamed: D13.2 (A), R125.1
unnamed: C122.1, D13.1 (K), Q27.3 (D), U62.3 (+)
unnamed: D15.2 (A), R136.1, U65.6
unnamed: C134.1, D15.1 (K), Q28.3 (D), U66.3 (+)
unnamed: J4.A5 (CC1), R30.2
unnamed: J4.B5 (CC2), R31.2
unnamed: J5.A5 (CC1), U25.1 (CC1)
unnamed: J5.B5 (CC2), U25.2 (CC2)
unnamed: J6.A5 (CC1), R42.2
unnamed: J6.B5 (CC2), R40.2
unnamed: C44.1, D6.1, J7.1 (In), R53.2
unnamed: C45.2, D7.1, J8.1 (In), R54.2
unnamed: J9.A5 (CC1), R60.2
unnamed: J9.B5 (CC2), R61.2
unnamed: J11.3, R64.2
unnamed: J11.4, R65.2
unnamed: Q1.1 (G), Q2.3 (C), R22.2
unnamed: Q1.2 (S), R21.1, R22.1, U22.9 (Vin-)
unnamed: Q2.1 (B), R23.2
unnamed: Q3.1 (G), Q4.3 (C), R26.2
unnamed: Q3.2 (S), R25.1, R26.1, U23.9 (Vin-)
unnamed: Q4.1 (B), R27.2
unnamed: Q5.1 (B), R34.2
unnamed: Q5.3 (C), R36.1
unnamed: Q6.1 (B), R35.2
unnamed: Q7.1 (B), R46.2
unnamed: Q7.3 (C), R48.1, U26.4 (EN)
unnamed: Q8.1 (B), R58.1
unnamed: Q8.3 (C), R55.2, U33.39 (PWRKEY)
unnamed: Q9.1 (G), R67.2, R68.2
unnamed: Q9.3 (S), R66.1, R67.1, U38.9 (Vin-)
unnamed: Q10.2 (B), R69.2
unnamed: Q10.1 (C), R68.1
unnamed: C65.1, C66.1, Q11.3 (S), Q12.3 (S), R71.1, R74.2, U39.1
unnamed: Q13.3 (D), Q14.3 (D), SW2.2
unnamed: Q13.1 (G), R73.2
unnamed: C67.1, Q14.1 (G), R74.1, R75.1
unnamed: Q15.1 (G), Q17.3 (C), R83.2
unnamed: Q15.2 (S), R81.1, R83.1, U41.9 (Vin-)
unnamed: Q16.1 (G), Q18.3 (C), R84.2
unnamed: Q16.2 (S), R82.1, R84.1, U42.9 (Vin-)
unnamed: Q17.1 (B), R85.2
unnamed: Q18.1 (B), R86.2
unnamed: Q19.1 (G), Q21.3 (C), R91.2
unnamed: Q19.2 (S), R89.1, R91.1, U43.9 (Vin-)
unnamed: Q20.1 (G), Q22.3 (C), R92.2
unnamed: Q20.2 (S), R90.1, R92.1, U44.9 (Vin-)
unnamed: Q21.1 (B), R93.2
unnamed: Q22.1 (B), R94.2
unnamed: Q23.1 (G), Q24.3 (C), R98.2
unnamed: Q23.2 (S), R97.1, R98.1, U45.9 (Vin-)
unnamed: Q24.1 (B), R99.2
unnamed: Q25.1 (G), Q26.1 (C), R102.2
unnamed: Q25.2 (S), R101.1, R102.1, U46.9 (Vin-)
unnamed: Q26.2 (B), R103.2
unnamed: Q27.1 (G), R120.2, R122.2
unnamed: Q28.1 (G), R131.2, R134.2
unnamed: R15.2, U18.E
unnamed: R16.2, U18.G
unnamed: R17.2, U18.J
unnamed: R106.2, R107.2, R108.2, R109.2, R110.2, R111.2, R112.2, R113.2
unnamed: R7.2, U4.2 (CD/DAT3)
unnamed: R8.1, U4.8 (DAT1)
unnamed: R9.2, U4.1 (DAT2)
unnamed: R12.2, U5.6 (1PPS)
unnamed: R11.2, U5.10 (~RESET)
unnamed: R13.2, U7.3 (ADDR)
unnamed: U7.9 (SCL_C), U11.2 (SCL)
unnamed: U7.1 (SDA_C), U11.1 (SDA)
unnamed: R14.2, U15.4 (REXT)
unnamed: C10.1, U19.4 (REGCAP)
unnamed: C14.2, U21.10 (CAP)
unnamed: R23.1, R24.2, U22.3 (~Alert)
unnamed: R27.1, R28.2, U23.3 (~Alert)
unnamed: J4.A6 (D+), J4.B6 (D+), U24.1 (UD+)
unnamed: J4.A7 (D-), J4.B7 (D-), U24.2 (UD-)
unnamed: R44.2, R45.1, U26.3 (FB)
unnamed: L1.1, U26.1 (LX)
unnamed: C32.1, U27.33 (VCORE)
unnamed: C28.2, U27.32 (XI), Y1.3
unnamed: C29.2, U27.31 (XO), Y1.1
unnamed: U33.2 (UART1_RXD), U34.7 (A1)
unnamed: U33.1 (UART1_TXD), U34.6 (A2)
unnamed: C56.2, R64.1, U37.5 (AIN1(+))
unnamed: C56.1, R65.1, U37.6 (AIN1(-))
unnamed: R69.1, R70.2, U38.3 (~Alert)
unnamed: C68.1, U40.1 (BST)
unnamed: C70.1, R77.1, U40.6 (COMP)
unnamed: C72.2, R78.2, R79.1, U40.5 (FB)
unnamed: C69.1, U40.4 (SS)
unnamed: L2.1, R76.1, U40.8 (SW)
unnamed: R85.1, R87.2, U41.3 (~Alert)
unnamed: R86.1, R88.2, U42.3 (~Alert)
unnamed: R93.1, R95.2, U43.3 (~Alert)
unnamed: R94.1, R96.2, U44.3 (~Alert)
unnamed: R99.1, R100.2, U45.3 (~Alert)
unnamed: R103.1, R104.2, U46.3 (~Alert)
unnamed: R114.2, R115.2, R116.1, U57.3 (FB)
unnamed: U58.21 (ADCIN), U58.22 (MUXOUT)
unnamed: R121.1, U61.3 (+)
unnamed: R126.2, R128.1, U63.3 (+)
unnamed: C123.1, R127.2, U63.1 (-)
unnamed: C133.1, U64.10 (C1+)
unnamed: C133.2, U64.9 (C1–)
unnamed: C129.1, U64.5 (CP)
unnamed: R132.1, U65.4 (+)
unnamed: C132.1, R135.1, U65.1 (FB)
unnamed: R136.2, R139.1, U67.3 (+)
VBAT: C47.1, C48.1, C49.1, CN2.39, FPC1.39, U33.34 (VBAT), U33.35 (VBAT), U34.1 (VCCB)

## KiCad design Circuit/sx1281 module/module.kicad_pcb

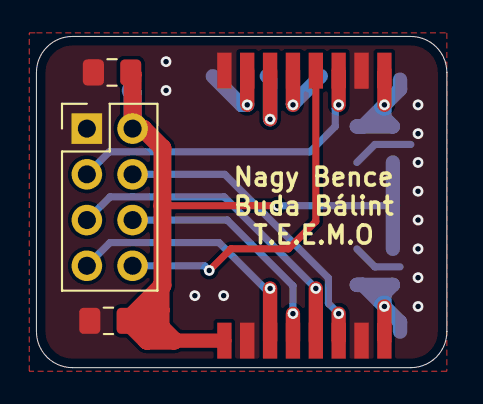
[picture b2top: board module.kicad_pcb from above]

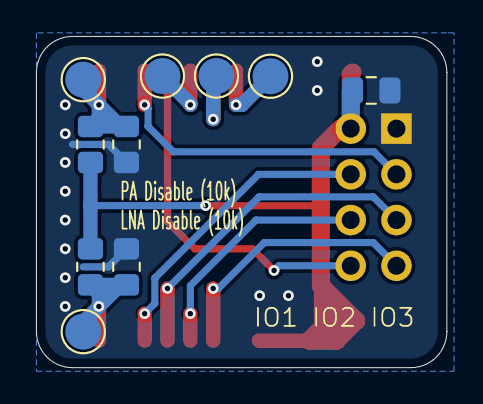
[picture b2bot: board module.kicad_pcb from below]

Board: 2 copper layers, 22.8 x 18.4 mm, 14 parts (10 on the bottom side), 13 nets.

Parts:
C2, C5, C6: C; C_0805_2012Metric_Pad1.18x1.45mm_HandSolder
J1: Conn_02x08_Counter_Clockwise; E28-2G4M27SX
J4: 2.4G_Radio; PinHeader_2x04_P2.54mm_Vertical
R1, R2, R3, R4: R; R_0805_2012Metric_Pad1.20x1.40mm_HandSolder
TP1, TP2, TP3, TP4, TP5: TestPoint; TestPoint_Pad_D2.0mm

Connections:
+3.3V: C2.1, C5.1, C6.1, J1.1, J4.2, R1.1, R3.1
/2.4g_cs: J1.6, J4.4
/2.4g_en: J1.11, J4.3
/2.4g_int: J1.12, J4.8
/IO1: J1.15, TP3.1
/IO2: J1.14, TP4.1
/IO3: J1.13, TP1.1
/LNA_EN: J1.8, R1.2, R2.1, TP5.1
/PA_EN: J1.9, R3.2, R4.1, TP2.1
/SPI_CLK: J1.5, J4.5
/SPI_MISO: J1.3, J4.7
/SPI_MOSI: J1.4, J4.6
GND: C2.2, C5.2, C6.2, J1.2, J1.7, J1.10, J1.16, J4.1, R2.2, R4.2

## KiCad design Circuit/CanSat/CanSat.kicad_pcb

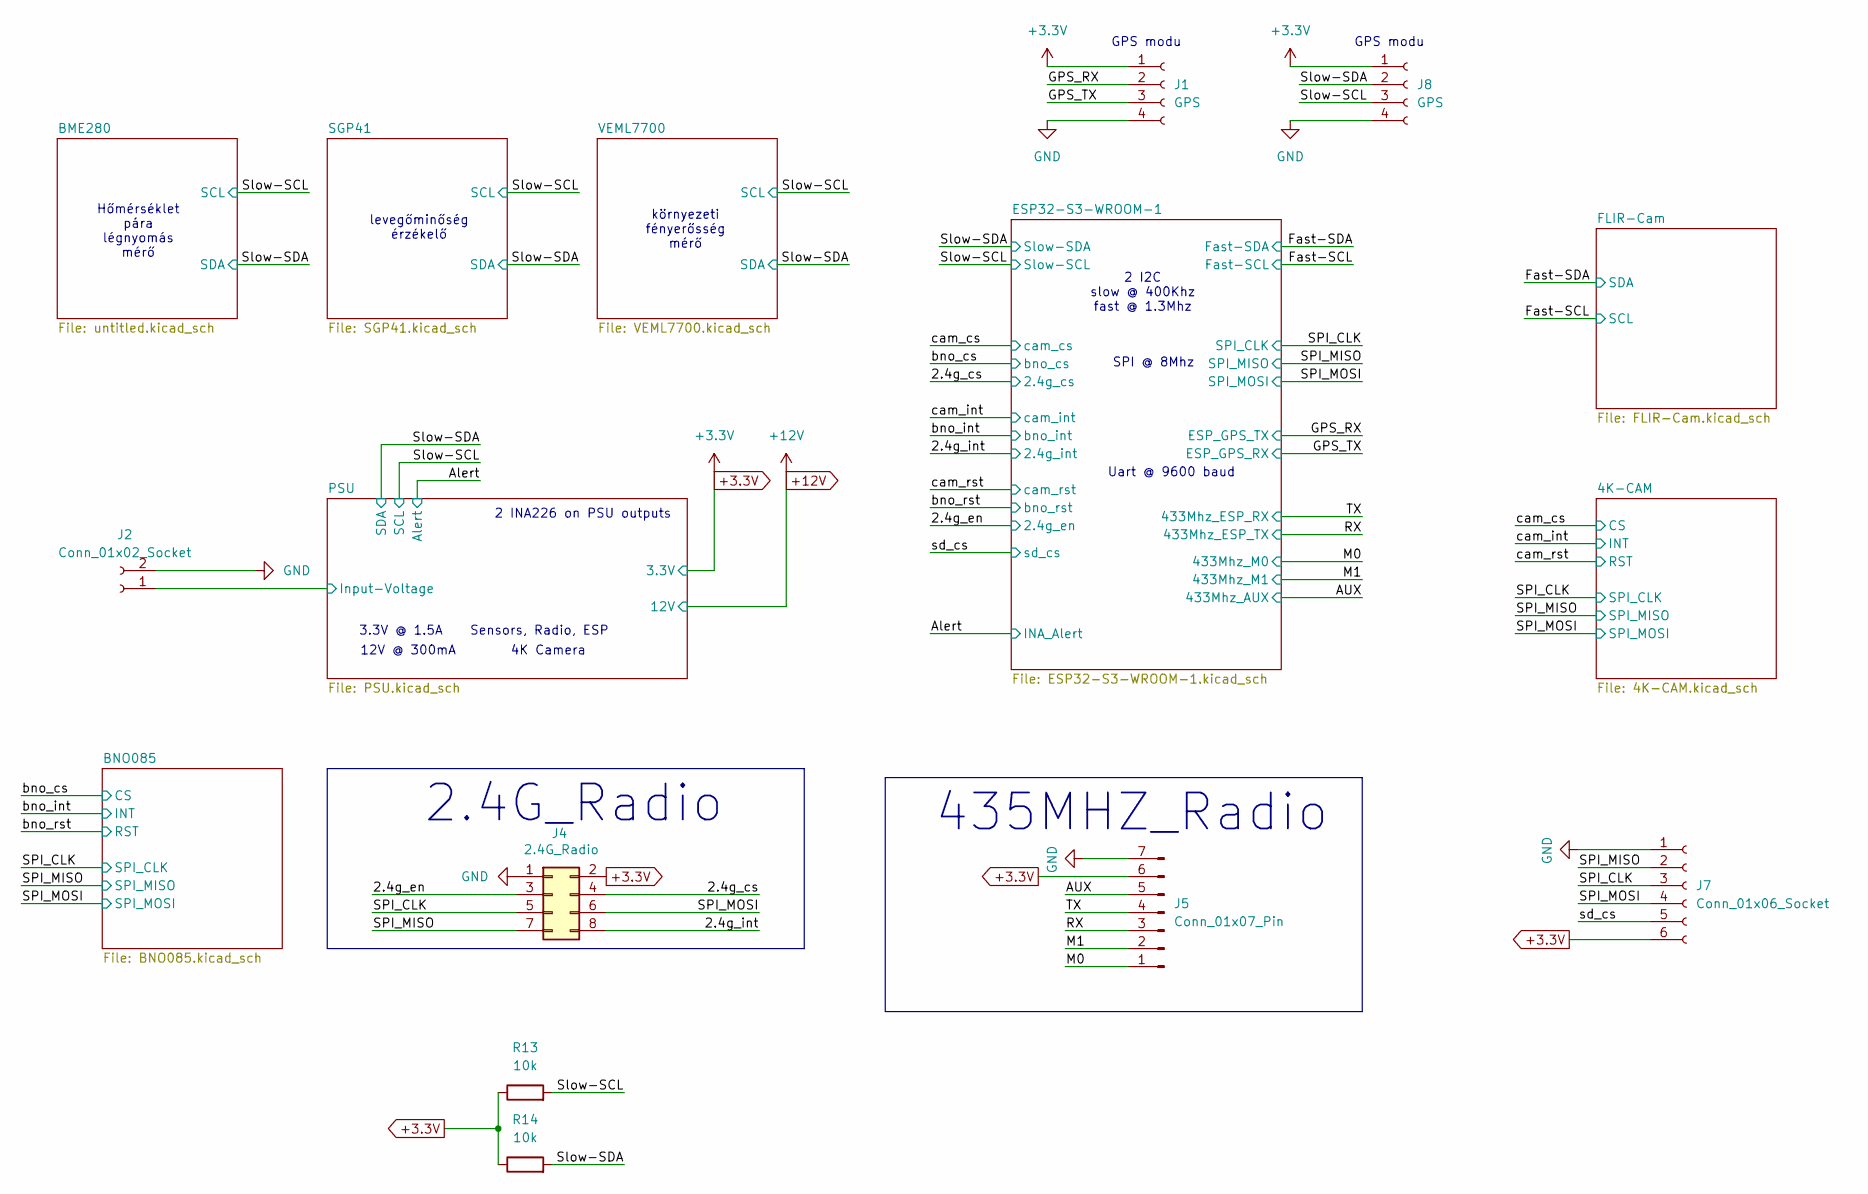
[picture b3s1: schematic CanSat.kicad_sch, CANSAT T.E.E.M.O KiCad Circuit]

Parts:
J1, J8: GPS; JST_PH_B4B-PH-K_1x04_P2.00mm_Vertical
J2: Conn_01x02_Socket; JST_PH_B2B-PH-K_1x02_P2.00mm_Vertical
J4: 2.4G_Radio; PinHeader_2x04_P2.54mm_Vertical
J5: Conn_01x07_Pin; PinHeader_1x07_P2.54mm_Vertical
J7: Conn_01x06_Socket; PinHeader_1x06_P2.54mm_Vertical
R13, R14: 10k; R_0805_2012Metric

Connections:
+3.3V: J1.1, J4.2, J5.6, J7.6, J8.1, R13.1, R14.1; also elsewhere on the board
/2.4g_cs: J4.4; also elsewhere on the board
/2.4g_en: J4.3; also elsewhere on the board
/2.4g_int: J4.8; also elsewhere on the board
/AUX: J5.5; also elsewhere on the board
/GPS_RX: J1.2; also elsewhere on the board
/GPS_TX: J1.3; also elsewhere on the board
/M0: J5.1; also elsewhere on the board
/M1: J5.2; also elsewhere on the board
/RX: J5.3; also elsewhere on the board
/SPI_CLK: J4.5, J7.3; also elsewhere on the board
/SPI_MISO: J4.7, J7.2; also elsewhere on the board
/SPI_MOSI: J4.6, J7.4; also elsewhere on the board
/Slow-SCL: J8.3, R13.2; also elsewhere on the board
/Slow-SDA: J8.2, R14.2; also elsewhere on the board
/TX: J5.4; also elsewhere on the board
/sd_cs: J7.5; also elsewhere on the board
GND: J1.4, J2.2, J4.1, J5.7, J7.1, J8.4; also elsewhere on the board

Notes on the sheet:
12V @ 300mA 4K Camera
SPI @ 8Mhz
környezeti fényerősség mérő
2 INA226 on PSU outputs
levegőminőség érzékelő
435MHZ_Radio
GPS modu
2 I2C slow @ 400Khz fast @ 1.3Mhz
Uart @ 9600 baud
2.4G_Radio
Hőmérséklet pára légnyomás mérő
3.3V @ 1.5A Sensors, Radio, ESP
